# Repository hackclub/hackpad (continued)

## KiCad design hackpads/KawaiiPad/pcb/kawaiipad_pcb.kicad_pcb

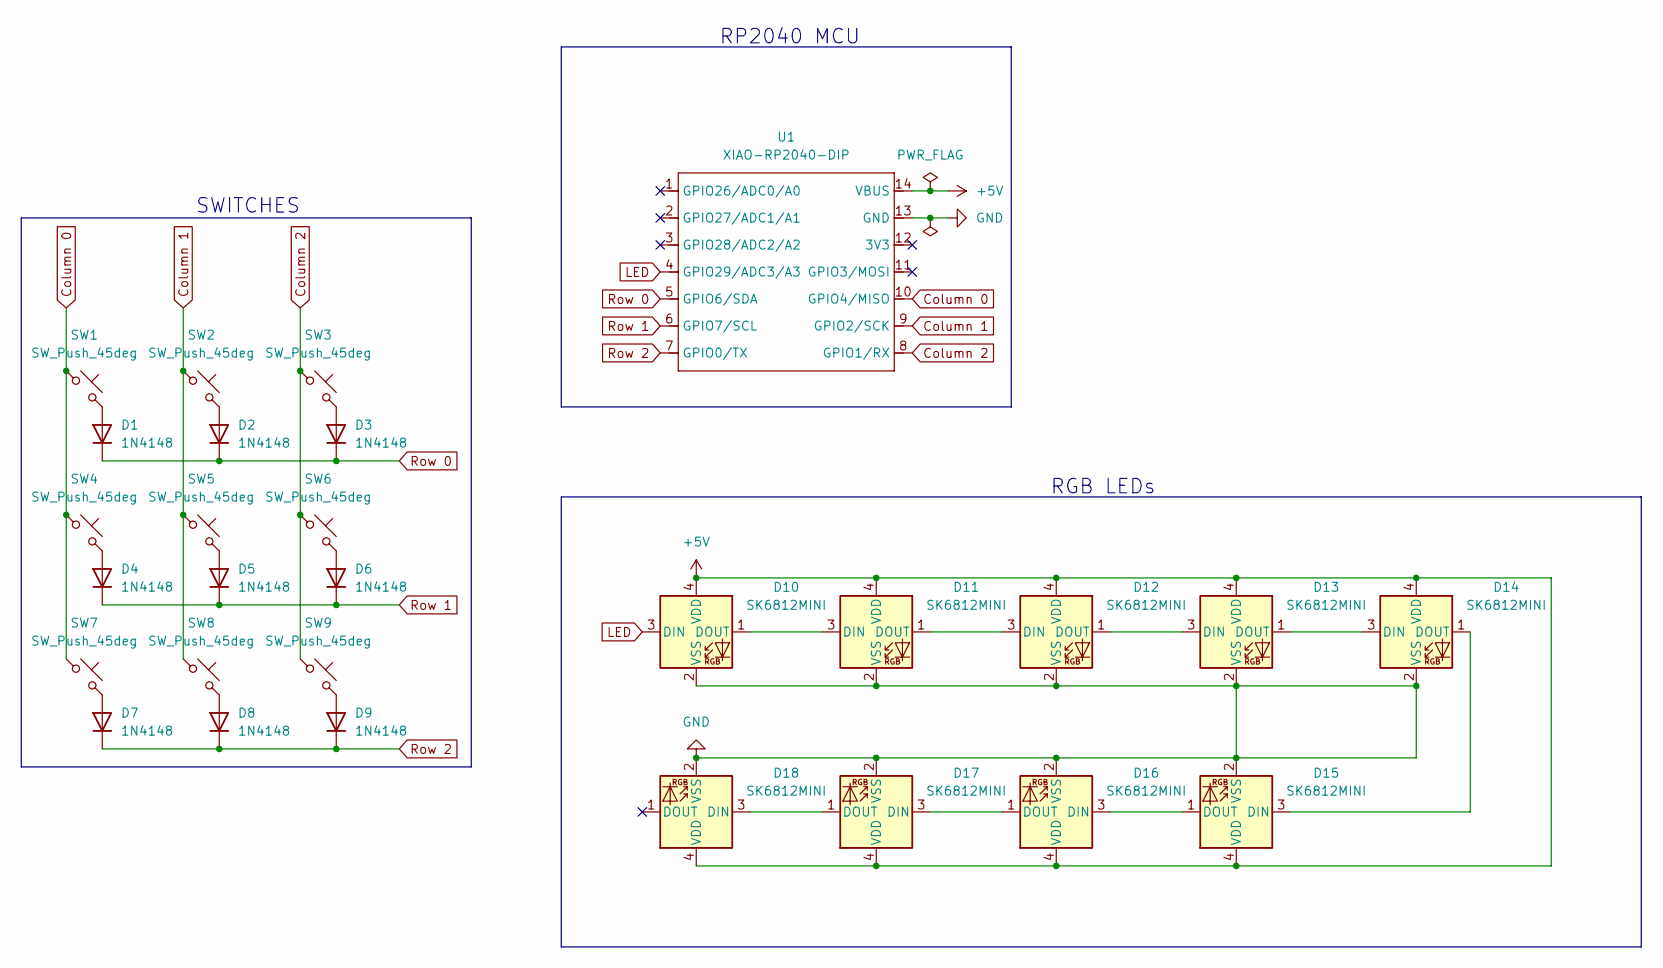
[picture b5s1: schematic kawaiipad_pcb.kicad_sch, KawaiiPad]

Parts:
D1, D2, D3, D4, D5, D6, D7, D8, D9: 1N4148; D_DO-35_SOD27_P7.62mm_Horizontal
D10, D11, D12, D13, D14, D15, D16, D17, D18: SK6812MINI; LED_SK6812MINI_PLCC4_3.5x3.5mm_P1.75mm
SW1, SW2, SW3, SW4, SW5, SW6, SW7, SW8, SW9: SW_Push_45deg; SW_Cherry_MX_1.00u_PCB
U1: XIAO-RP2040-DIP

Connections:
+5V: D10.4 (VDD), D11.4 (VDD), D12.4 (VDD), D13.4 (VDD), D14.4 (VDD), D15.4 (VDD), D16.4 (VDD), D17.4 (VDD), D18.4 (VDD), U1.14 (VBUS)
Column 0: SW1.1, SW4.1, SW7.1, U1.10 (GPIO4/MISO)
Column 1: SW2.1, SW5.1, SW8.1, U1.9 (GPIO2/SCK)
Column 2: SW3.1, SW6.1, SW9.1, U1.8 (GPIO1/RX)
GND: D10.2 (VSS), D11.2 (VSS), D12.2 (VSS), D13.2 (VSS), D14.2 (VSS), D15.2 (VSS), D16.2 (VSS), D17.2 (VSS), D18.2 (VSS), U1.13 (GND)
LED: D10.3 (DIN), U1.4 (GPIO29/ADC3/A3)
unnamed: D1.2 (A), SW1.2
unnamed: D2.2 (A), SW2.2
unnamed: D3.2 (A), SW3.2
unnamed: D4.2 (A), SW4.2
unnamed: D5.2 (A), SW5.2
unnamed: D6.2 (A), SW6.2
unnamed: D7.2 (A), SW7.2
unnamed: D8.2 (A), SW8.2
unnamed: D9.2 (A), SW9.2
unnamed: D10.1 (DOUT), D11.3 (DIN)
unnamed: D11.1 (DOUT), D12.3 (DIN)
unnamed: D12.1 (DOUT), D13.3 (DIN)
unnamed: D13.1 (DOUT), D14.3 (DIN)
unnamed: D14.1 (DOUT), D15.3 (DIN)
unnamed: D15.1 (DOUT), D16.3 (DIN)
unnamed: D16.1 (DOUT), D17.3 (DIN)
unnamed: D17.1 (DOUT), D18.3 (DIN)
Row 0: D1.1 (K), D2.1 (K), D3.1 (K), U1.5 (GPIO6/SDA)
Row 1: D4.1 (K), D5.1 (K), D6.1 (K), U1.6 (GPIO7/SCL)
Row 2: D7.1 (K), D8.1 (K), D9.1 (K), U1.7 (GPIO0/TX)

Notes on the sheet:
SWITCHES
RGB LEDs
RP2040 MCU

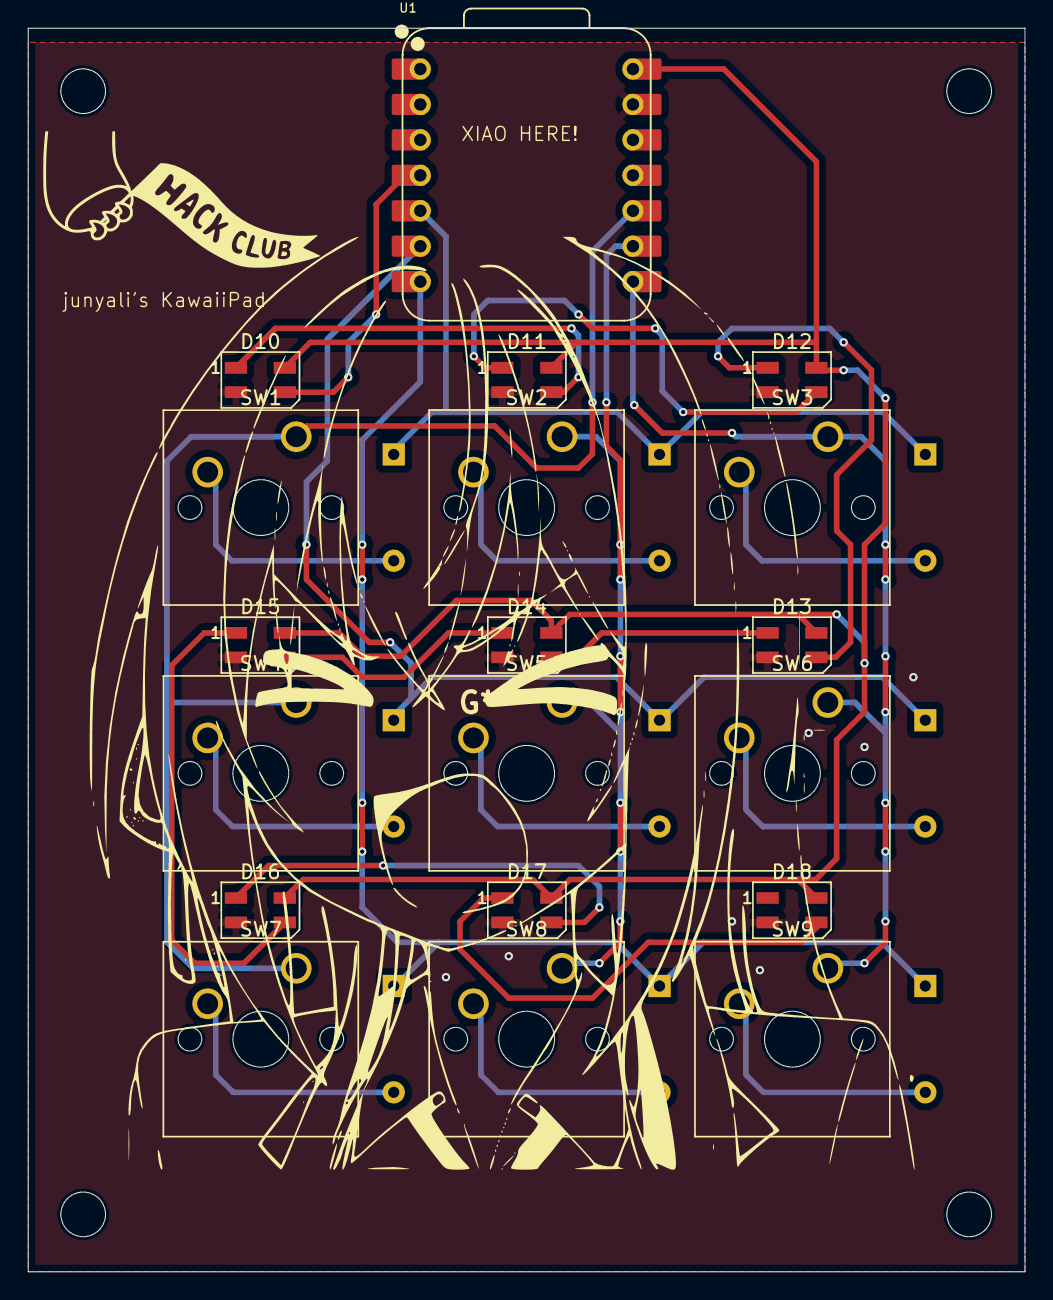
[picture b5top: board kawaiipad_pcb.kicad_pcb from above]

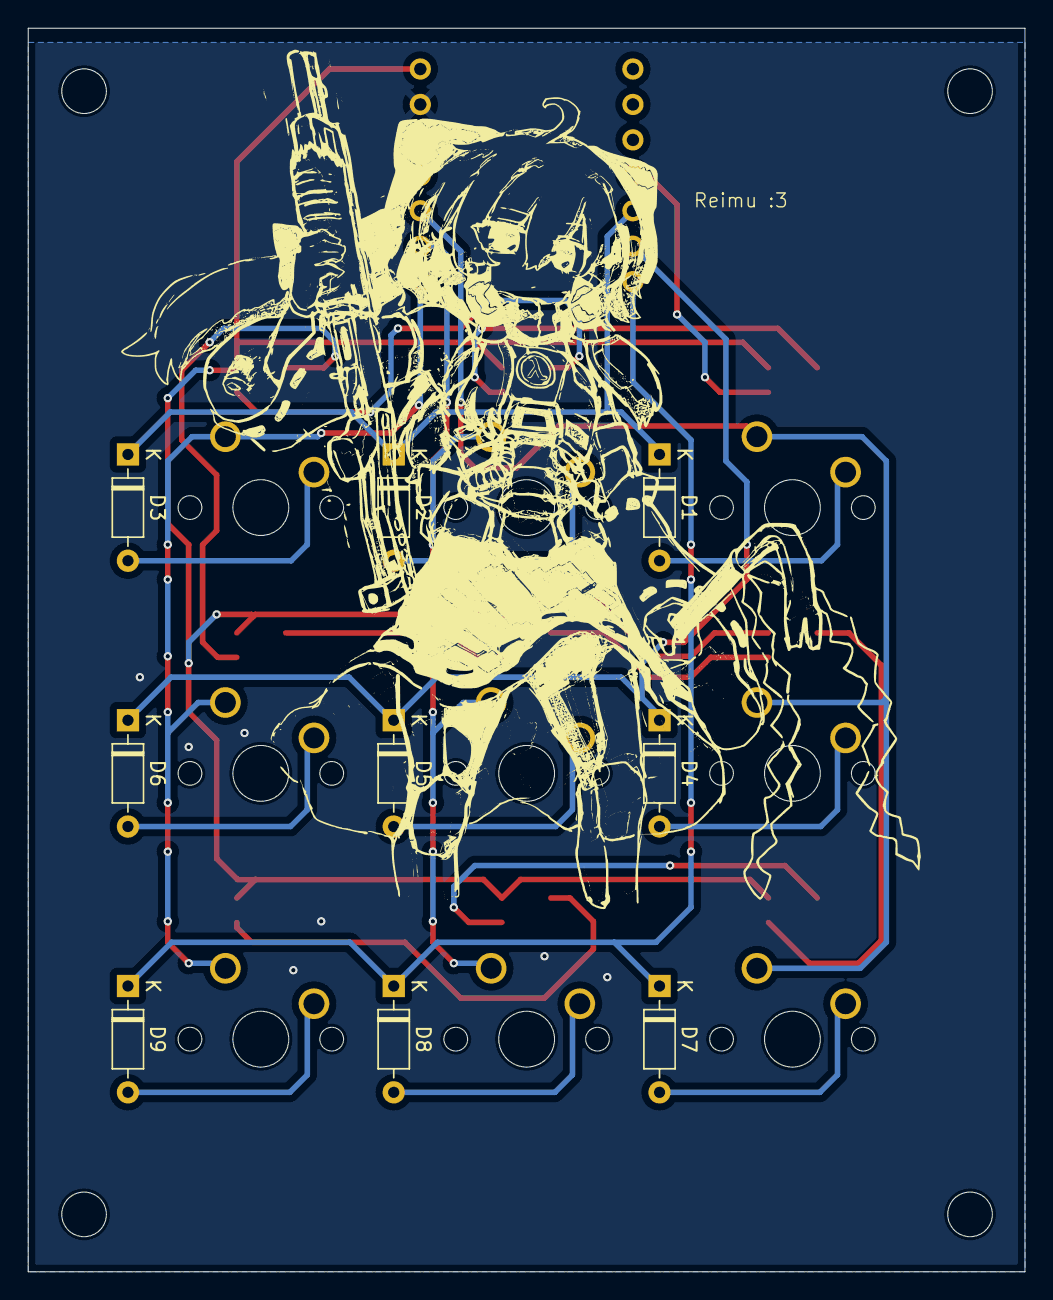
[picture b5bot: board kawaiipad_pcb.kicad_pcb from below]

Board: 2 copper layers, 71.4 x 89.1 mm, 28 parts (9 on the bottom side), 26 nets.

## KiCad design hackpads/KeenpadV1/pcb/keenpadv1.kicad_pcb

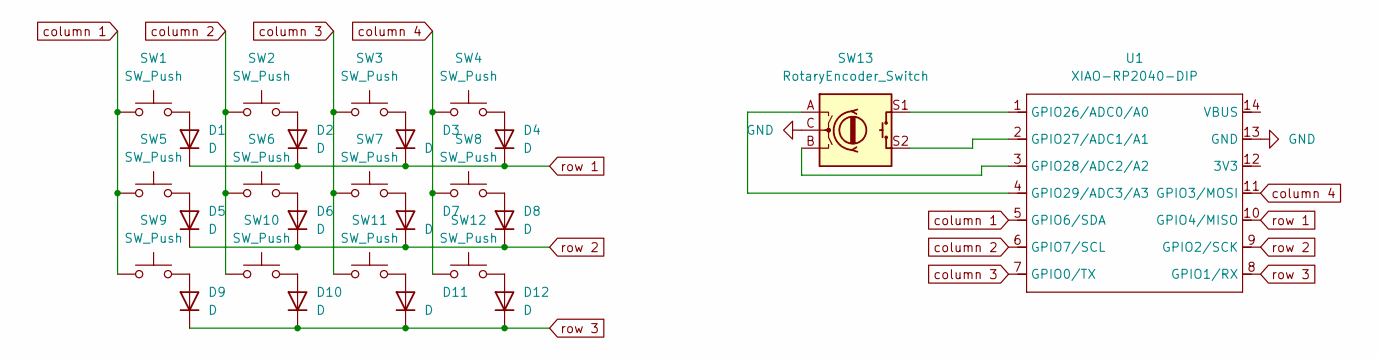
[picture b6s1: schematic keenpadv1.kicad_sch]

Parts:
D1, D2, D3, D4, D5, D6, D7, D8, D9, D10, D11, D12: D; DIODE-1N4148
SW1, SW2, SW3, SW4, SW5, SW6, SW7, SW8, SW9, SW10, SW11, SW12: SW_Push; SW_Cherry_MX_1.00u_PCB
SW13: RotaryEncoder_Switch; RotaryEncoder_Alps_EC11E-Switch_Vertical_H20mm_CircularMoun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
U1: XIAO-RP2040-DIP; MOUDLE14P-XIAO-DIP-SMD

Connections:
GND: SW13.C, U1.13 (GND)
unnamed: D1.2 (A), SW1.2
unnamed: D2.2 (A), SW2.2
unnamed: D3.2 (A), SW3.2
unnamed: D4.2 (A), SW4.2
unnamed: D5.2 (A), SW5.2
unnamed: D6.2 (A), SW6.2
unnamed: D7.2 (A), SW7.2
unnamed: D8.2 (A), SW8.2
unnamed: D9.2 (A), SW9.2
unnamed: D10.2 (A), SW10.2
unnamed: D11.2 (A), SW11.2
unnamed: D12.2 (A), SW12.2
unnamed: SW13.S1, U1.1 (GPIO26/ADC0/A0)
unnamed: SW13.S2, U1.2 (GPIO27/ADC1/A1)
unnamed: SW13.B, U1.3 (GPIO28/ADC2/A2)
unnamed: SW13.A, U1.4 (GPIO29/ADC3/A3)
column 1: SW1.1, SW5.1, SW9.1, U1.5 (GPIO6/SDA)
column 2: SW2.1, SW6.1, SW10.1, U1.6 (GPIO7/SCL)
column 3: SW3.1, SW7.1, SW11.1, U1.7 (GPIO0/TX)
column 4: SW4.1, SW8.1, SW12.1, U1.11 (GPIO3/MOSI)
row 1: D1.1 (K), D2.1 (K), D3.1 (K), D4.1 (K), U1.10 (GPIO4/MISO)
row 2: D5.1 (K), D6.1 (K), D7.1 (K), D8.1 (K), U1.9 (GPIO2/SCK)
row 3: D9.1 (K), D10.1 (K), D11.1 (K), D12.1 (K), U1.8 (GPIO1/RX)

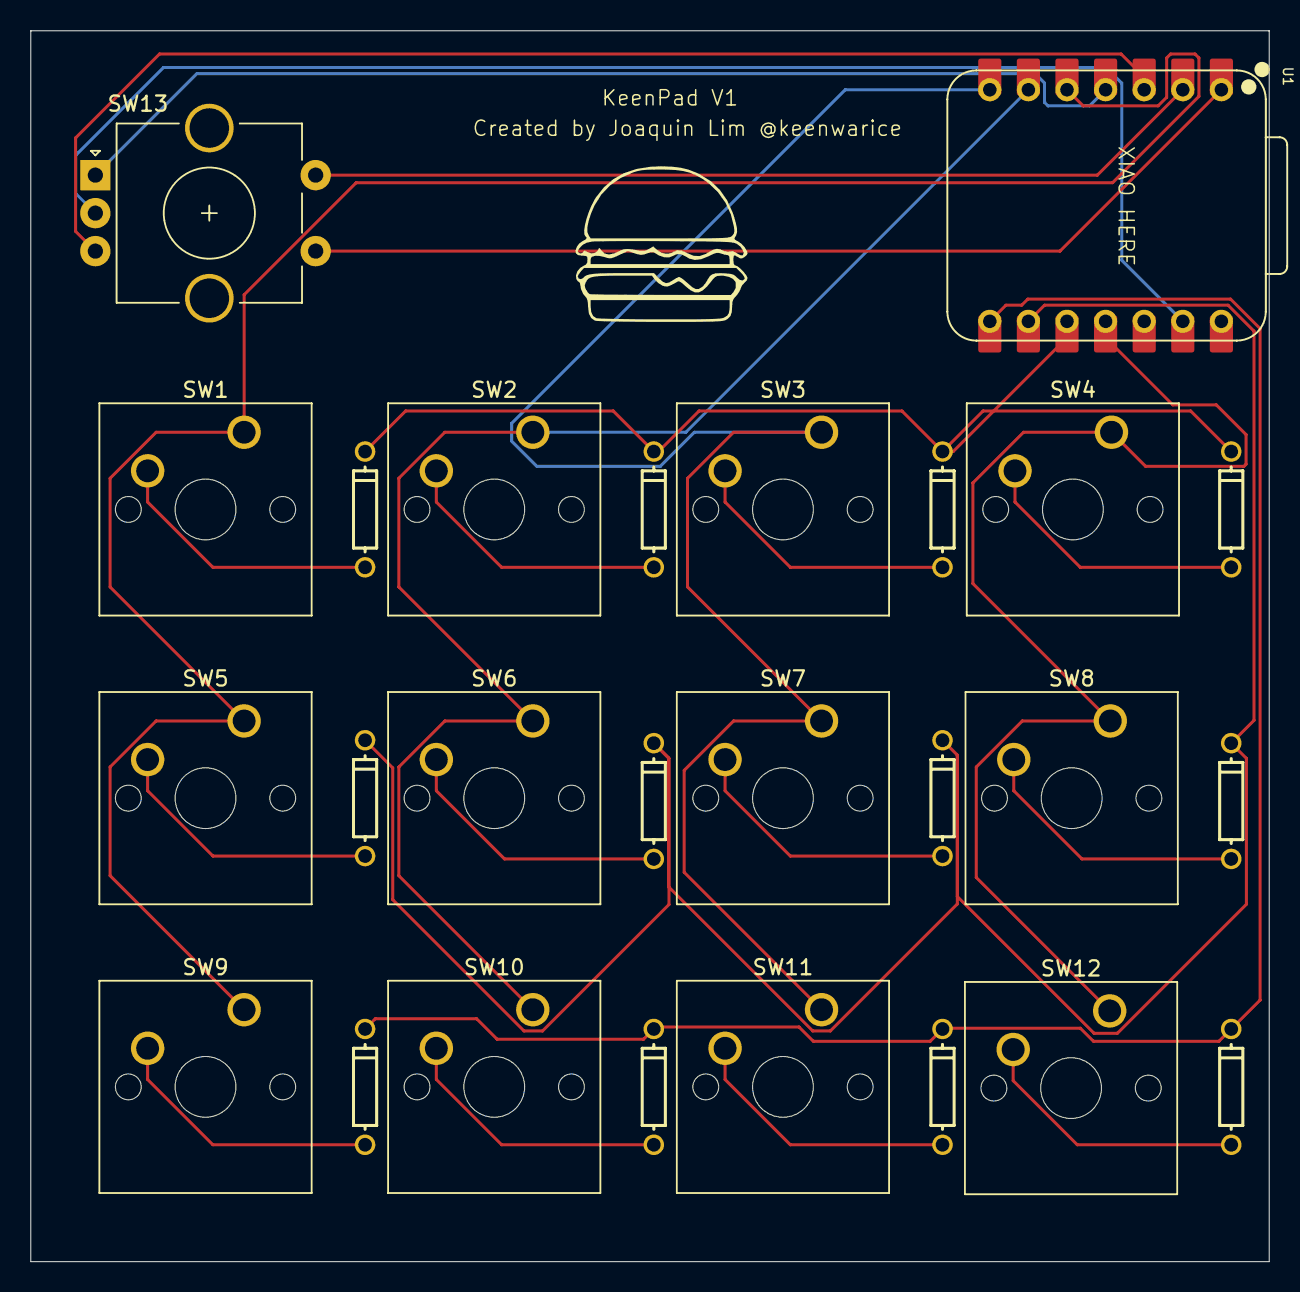
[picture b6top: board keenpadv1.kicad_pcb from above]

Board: 2 copper layers, 81.5 x 81.0 mm, 26 parts (0 on the bottom side), 24 nets.
